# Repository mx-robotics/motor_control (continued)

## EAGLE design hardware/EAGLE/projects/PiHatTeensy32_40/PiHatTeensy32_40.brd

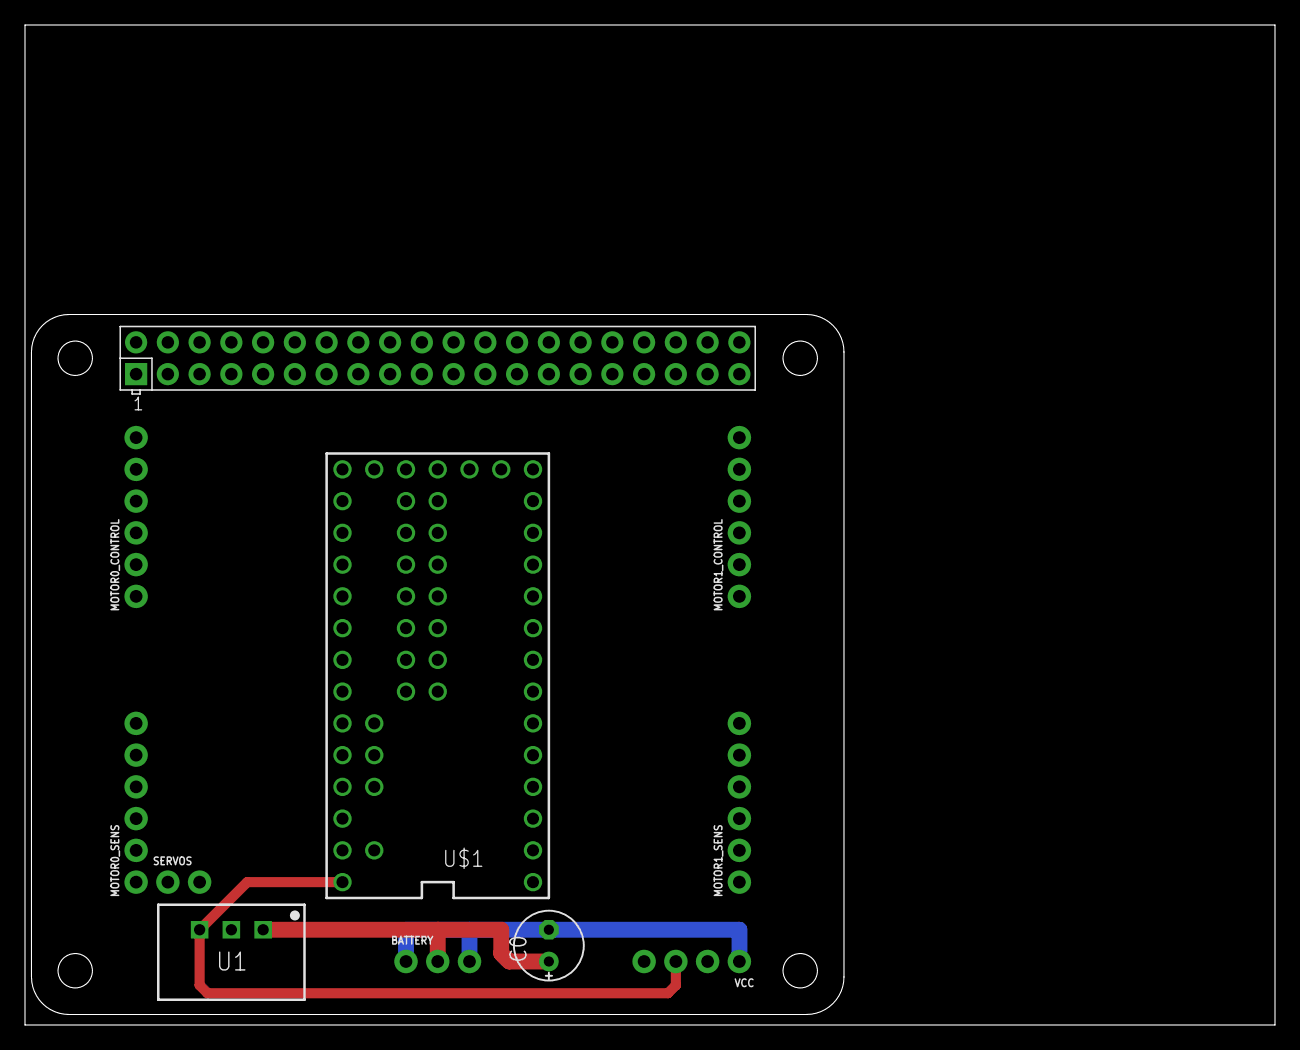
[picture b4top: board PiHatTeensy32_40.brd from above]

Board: 2 copper layers, 100.0 x 80.0 mm, 11 parts (0 on the bottom side), 31 nets.

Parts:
BATTERY: 1X03_NO_SILK
C0: E2,5-6E
MOTOR0_CONTROL, MOTOR0_SENS, MOTOR1_CONTROL, MOTOR1_SENS: 1X06_NO_SILK
SERVOS: 1X02_NO_SILK
U1: TSR_1-2450; TSR-1
U$1: TEENSY_3.1-3.2_ALL_PINS&PADS; TEENSY_3.0-3.2_ALL_PINS_&_PADS
VCC: JP; 1X04_NO_SILK
X1: RASPI_BOARD_B+_H; RASPI_BOARD_B+HAT

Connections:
3.3V: U$1.3.3V, U$1.3.3V1, U$1.3.3V2, VCC.2
5.0V: U1.3, U$1.VIN, VCC.3
GND: BATTERY.1, BATTERY.3, C0.-, U1.2, U$1.GND, U$1.GND1, U$1.GND2, VCC.1, X1.6
HALL_U0: MOTOR0_SENS.1, U$1.0
HALL_U1: MOTOR1_SENS.1, U$1.1
HALL_V0: MOTOR0_SENS.2, U$1.24
HALL_V1: MOTOR1_SENS.2, U$1.2
HALL_W0: MOTOR0_SENS.3, U$1.33
HALL_W1: MOTOR1_SENS.3, U$1.4
I2C0_SCL: U$1.29, X1.5
I2C0_SDA: U$1.30, X1.3
IN_U0: MOTOR0_CONTROL.4, U$1.23/A9
IN_U1: MOTOR1_CONTROL.4, U$1.5
IN_V0: MOTOR0_CONTROL.5, U$1.22/A8
IN_V1: MOTOR1_CONTROL.5, U$1.6
IN_W0: MOTOR0_CONTROL.6, U$1.21/A7
IN_W1: MOTOR1_CONTROL.6, U$1.10
IS_U0: MOTOR0_SENS.4, U$1.20/A6
IS_U1: MOTOR1_SENS.4, U$1.26
IS_V0: MOTOR0_SENS.5, U$1.19/A5
IS_V1: MOTOR1_SENS.5, U$1.27
IS_W0: MOTOR0_SENS.6, U$1.18/A4
IS_W1: MOTOR1_SENS.6, U$1.28
SERVO_0: SERVOS.1, U$1.32
SERVO_1: SERVOS.2, U$1.25
SPI_CS0: U$1.15/A1, X1.24
SPI_CS1: U$1.31, X1.26
SPI_MISO: U$1.12, X1.21
SPI_MOSI: U$1.11, X1.19
SPI_SCLK: U$1.14/A0, X1.23
VI: BATTERY.2, C0.+, U1.1

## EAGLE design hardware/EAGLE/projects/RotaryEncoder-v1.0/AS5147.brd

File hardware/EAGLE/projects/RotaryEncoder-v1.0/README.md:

PCB for AMS (Austrian Micro Devices) Magnetic Position Sensors.

The physical interface fits the following devices:

1) AS5147P (https://ams.com/as5147p)

2) AS5047P (https://ams.com/as5047p)

3) AS5147 (https://ams.com/as5147)

4) AS5047D (https://ams.com/as5047d)

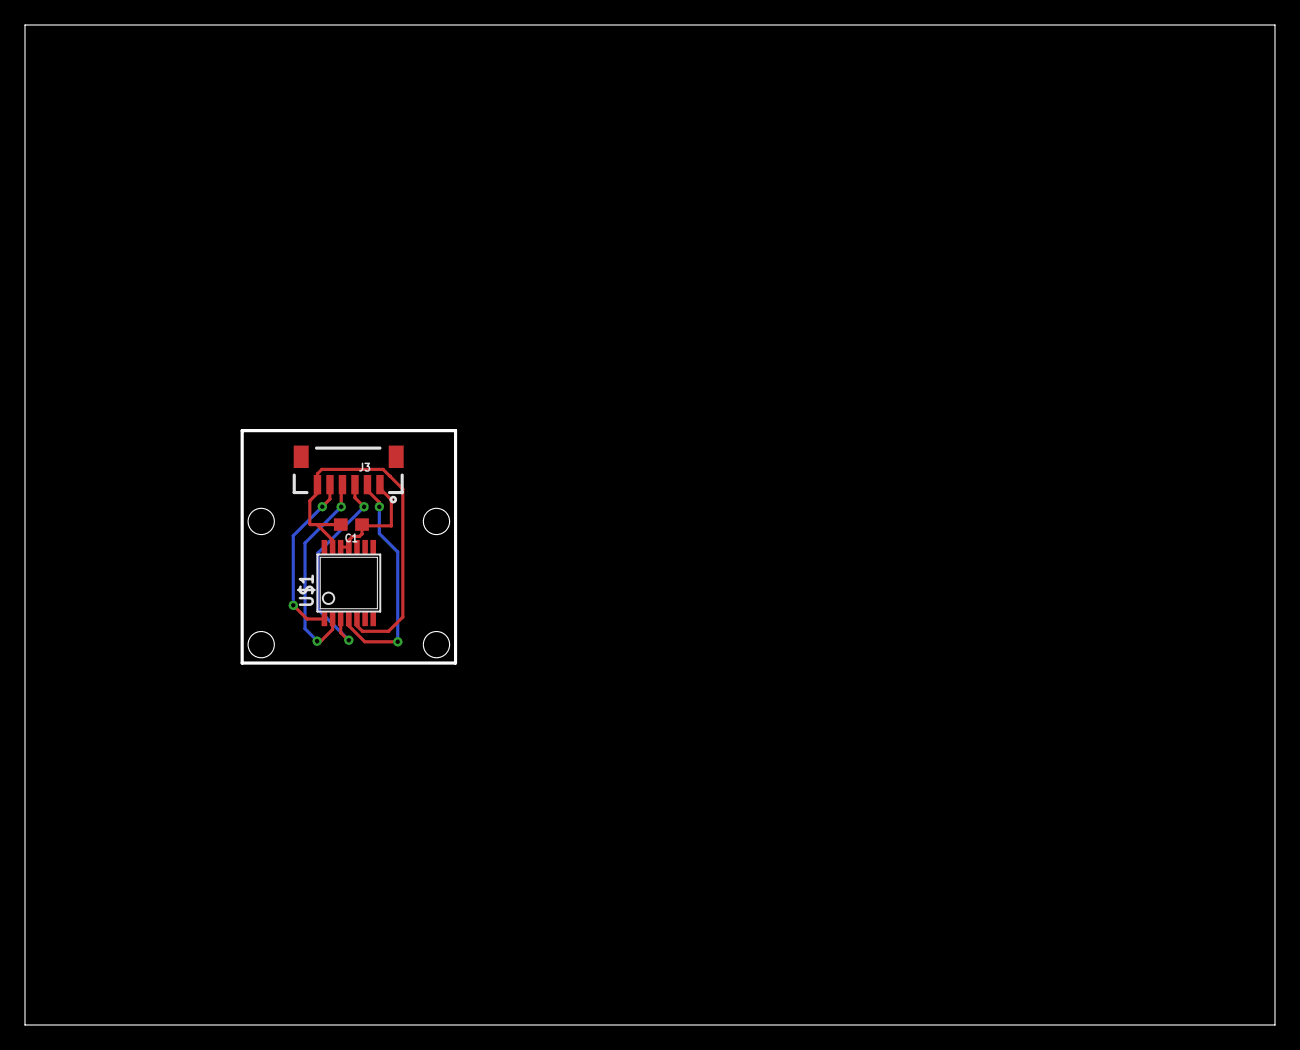
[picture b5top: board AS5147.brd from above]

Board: 2 copper layers, 100.0 x 80.0 mm, 3 parts (0 on the bottom side), 6 nets.

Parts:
C1: 0.1uF; 0603
J3: 1X06-1MM
U$1: TSSOP14

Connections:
3.3V: C1.1, J3.1, U$1.11, U$1.12
CLK: J3.4, U$1.2
CS: J3.5, U$1.1
GND: C1.2, J3.6, U$1.5, U$1.13
MISO: J3.3, U$1.3
MOSI: J3.2, U$1.4

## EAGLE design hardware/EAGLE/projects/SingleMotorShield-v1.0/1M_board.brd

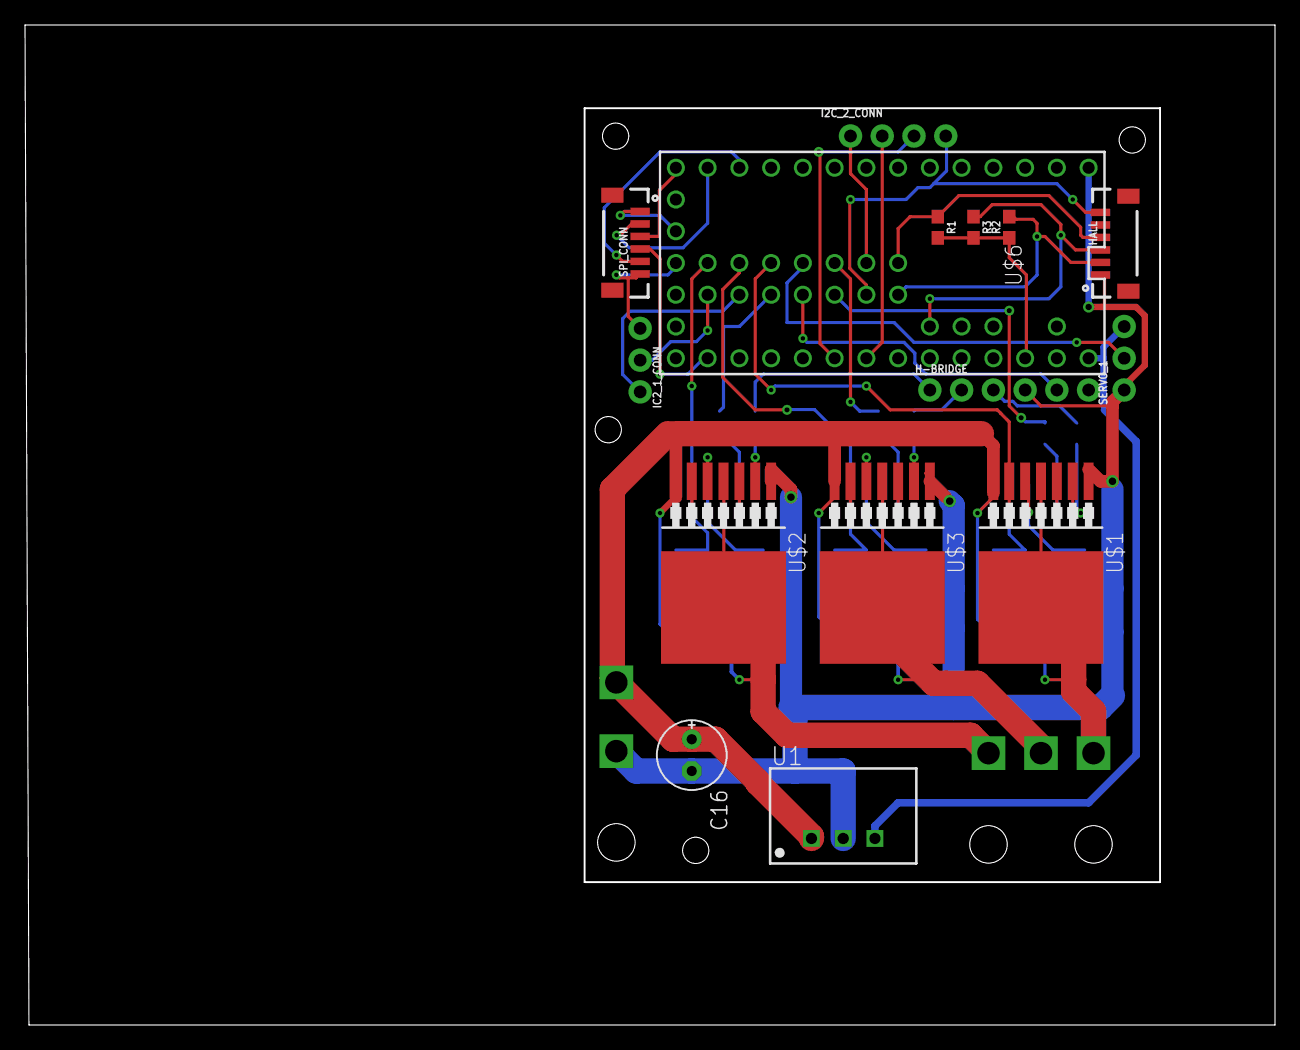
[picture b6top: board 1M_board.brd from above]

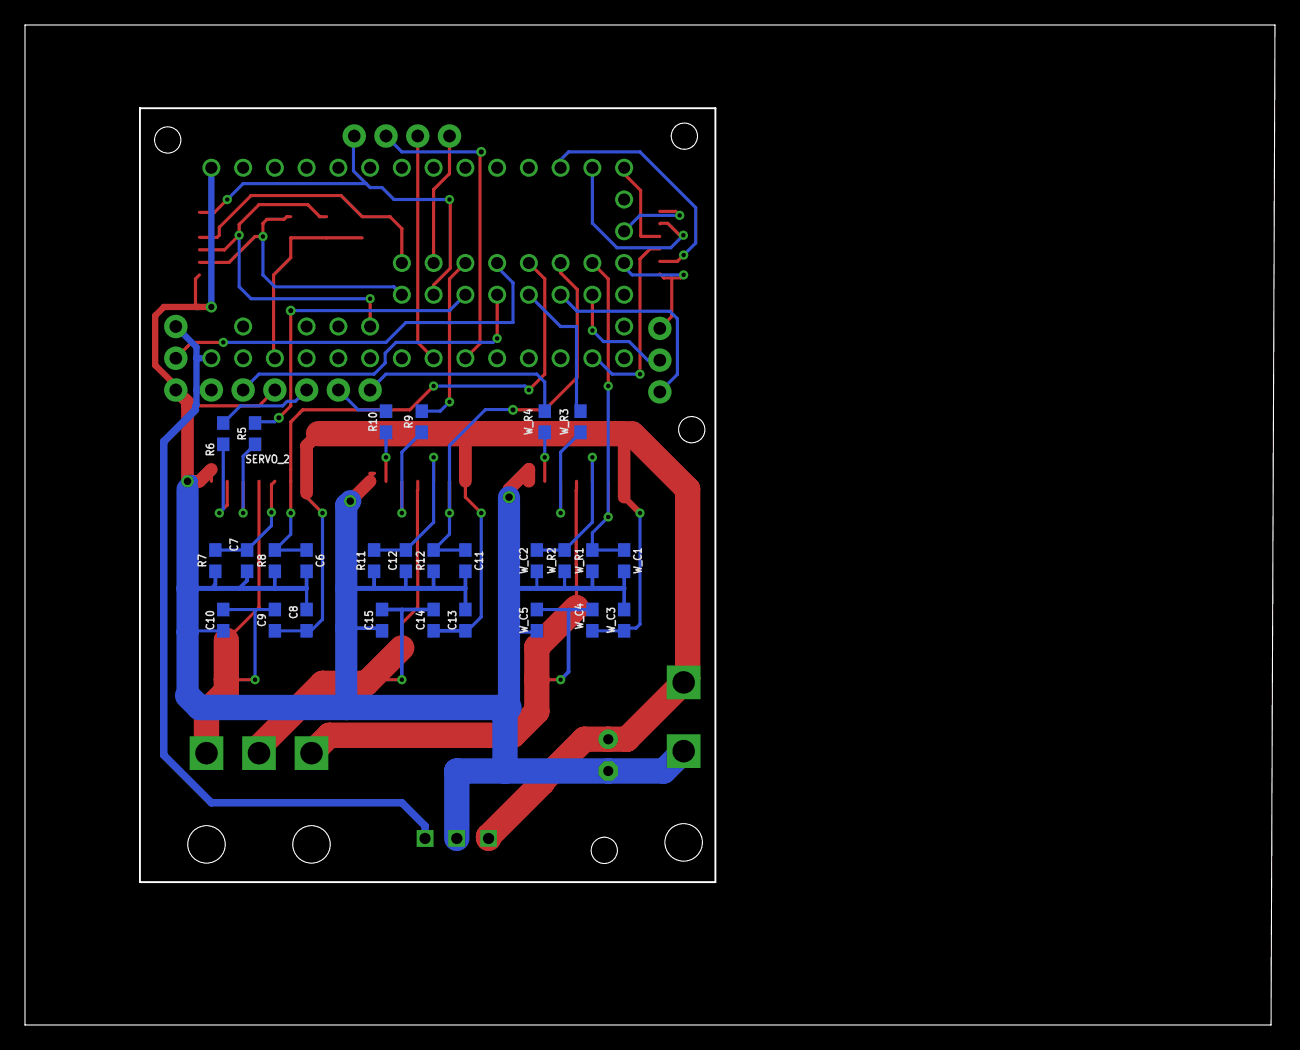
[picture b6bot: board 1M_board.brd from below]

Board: 2 copper layers, 100.0 x 80.0 mm, 45 parts (30 on the bottom side), 38 nets.

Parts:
C6, C8, C11, C13: 0.1uF; 0603
C7, C12: 1nF; 0603
C9, C10, C14, C15: 0.22uF; 0603
C16: 470uF; E2,5-6E
H-BRIDGE: PWM; 1X03_NO_SILK
HALL: 1X06-1MM
I2C_2_CONN: IMU_SENS; 1X04_NO_SILK
IC2_1_CONN: INTEL_BRD; 1X03_NO_SILK
R1, R2, R3, R5, R6, R9, R10: 10k; 0603
R7, R11: 47k; 0603
R8, R12: 4.7k; 0603
SERVO_1, SERVO_2: 1X03_NO_SILK
SPI_CONN: ENCODER; 1X06-1MM
U1: TSR_1-2450; TSR-1
U$1, U$2, U$3: P-TO263-7-1
U$4: 5569-003
U$5: 5569-002
U$6: TEENSY_3.1-3.2_ALL_PINS&PADS; TEENSY_3.0-3.2_ALL_PINS_&_PADS
W_C1, W_C3: 0.1uF; 0603
W_C2: 1nF; 0603
W_C4, W_C5: 0.22uF; 0603
W_R1: 4.7k; 0603
W_R2: 47k; 0603
W_R3, W_R4: 10k; 0603

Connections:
3.3V: HALL.6, I2C_2_CONN.4, R1.2, R2.1, R3.2, SPI_CONN.1, U$6.3.3V, U$6.3.3V1, U$6.3.3V2
CS: SPI_CONN.5, U$6.10
GND: C6.2, C7.1, C8.2, C10.1, C11.2, C12.1, C13.2, C15.1, C16.-, HALL.1, I2C_2_CONN.1, IC2_1_CONN.3, R7.1, R8.1, R11.1, R12.1, SERVO_1.1, SERVO_2.1, SPI_CONN.6, U1.2, U$1.1, U$2.1, U$3.1, U$5.GND, U$6.GND, U$6.GND1, U$6.GND2, W_C1.2, W_C2.1, W_C3.2, W_C5.1, W_R1.1, W_R2.1
HALL_U: HALL.4, R1.1, U$6.A12
HALL_V: HALL.3, R3.1, U$6.A11
HALL_W: HALL.2, R2.2, U$6.A13
INH_U: R5.2, U$6.33
INH_V: R9.2, U$6.24
INH_W: U$6.31, W_R3.2
IN_U: H-BRIDGE.3, R6.2
IN_V: H-BRIDGE.2, R10.2
IN_W: H-BRIDGE.1, W_R4.2
IS_U: C6.1, R8.2, U$1.6, U$6.26
IS_V: C11.1, R12.2, U$3.6, U$6.27
IS_W: U$2.6, U$6.28, W_C1.1, W_R1.2
MISO: SPI_CONN.3, U$6.12
MOSI: SPI_CONN.2, U$6.11
unnamed: U$2.3, W_R3.1
unnamed: C12.2, R11.2, U$3.5
unnamed: U$2.5, W_C2.2, W_R2.2
unnamed: C7.2, R7.2, U$1.5
unnamed: R5.1, U$1.3
unnamed: R6.1, U$1.2
unnamed: R9.1, U$3.3
unnamed: U$2.2, W_R4.1
unnamed: R10.1, U$3.2
SCK: SPI_CONN.4, U$6.14/A0
SCL0: I2C_2_CONN.2, U$6.19/A5
SCL1: IC2_1_CONN.2, U$6.29
SDA0: I2C_2_CONN.3, U$6.18/A4
SDA1: IC2_1_CONN.1, U$6.30
S_PWM_1: SERVO_1.2, U$6.25
S_PWM_2: SERVO_2.2, U$6.32
U: C9.2, C10.2, U$1.4, U$1.8, U$4.U
V: C14.2, C15.2, U$3.4, U$3.8, U$4.V
VCC: SERVO_1.3, SERVO_2.3, U1.3, U$6.VIN
VI: C8.1, C9.1, C13.1, C14.1, C16.+, U1.1, U$1.7, U$2.7, U$3.7, U$5.VCC, W_C3.1, W_C4.1
W: U$2.4, U$2.8, U$4.W, W_C4.2, W_C5.2

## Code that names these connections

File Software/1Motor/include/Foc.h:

//
// Created by firat on 19.01.20.
//
#ifndef DMA_SPI_FOC_H
#define DMA_SPI_FOC_H


#include <SPI.h>
#include <array>
#include <ADC.h>


namespace tuw {

    class FOC {
    public:
        static FOC &getInstance();  // Singleton handler

        void SPITransfer();

        void calculate_offset_parameters();
        void initPins();  // called once in setup
        void doTheMagic(); // called every loop iteration

        void P_controller(float rps_target, float rps_measured);
        void PID_controller(float rps_target, float rps_measured);



        // ########### PID RELATED FUNCTIONS ///////////

        void setSpeedRPM(uint8_t _target_speed);

        // ############# ADC

        void setSpeedFromADC();


        // ######### DEBUG FUNCTIONS ///////

        void printLUToffsetValues();
        void printMaxDutyCylcle();
        void setSpeedSerial();
        void debugPlot();
        std::array<uint16_t , 360> getArray();
        uint16_t getRotorPosition();
        float getMySpeed() const;
        volatile float getTargetSpeed() const;

        void led_foo ();
        void calculateSensorOffsetAngle();
        void getModulationIndexSpeedValues();

        void calculateRPS();








    private:
        FOC();

        // ++++++++++++++initial activation functios
        void initSPI();
        void initInhibitPIN();
        void setPWMpins();
        void initServoPins();
        void activateInhibitPins();

        // ***************** LUT & DUTY CYCLE CALCULATIONS
        void calculateInputPinsDutyCycle(); // on the fly calculation, used once for LUT creation
        inline uint16_t calculate_LUT_offset(); // calculate the modulation index-speed command relation
        std::array<uint16_t , 360> createLUT(); // create the LUT
        void calculate_offset_parameters_short(); // calculates the offset func parameters in a magic way, called 1
        void calculateInputPinsDutyCycleLUT();
        void setInputPinsDutyCycle();

        // ****************** ADC functions
        void initADCconversions();




        // ****************** MATH

        inline int fast_mod(const int input, const int ceil) {
            return input >= ceil ? input % ceil : input; }

        inline float moving_ave(float angle){
            static int i=0;
            static float sum = 0;
            sum -= move_average_list[i];
            move_average_list[i] = angle;
            sum += move_average_list[i];
            i++;
            if (i == 100) {
                i = 0;
            }

            return sum*0.01f;

        }

        // ************* P I N S ******************
        static constexpr uint8_t CS = 10; // has to be static cuz a constexpr must be known at compile time
        static constexpr uint8_t CLK = 14; // if it isn't static, you need to wait runtime until the object is created
        volatile uint16_t rotor_position=0;
        volatile float_t target_rpm=50.f;

        float_t offset_param_m;
        float_t offset_param_c;


        static constexpr uint8_t IS_W= A17;
        static constexpr uint8_t IS_v= A16;
        static constexpr uint8_t IS_U= A15;

        static constexpr uint8_t INH_W= 31;
        static constexpr uint8_t INH_V= 24;
        static constexpr uint8_t INH_U= 33;

        static constexpr uint8_t S_PWM1= 25;
        static constexpr uint8_t S_PWM2= 32;

        static constexpr uint8_t IN_W= 21;
        static constexpr uint8_t IN_V= 22;
        static constexpr uint8_t IN_U= 23;

        // *************** P W M   C O N S T A N T S ****************

        static constexpr uint16_t PWM_FREQ = 20000;
        static constexpr uint16_t MAX_DUTY_CYCLE = (F_BUS/PWM_FREQ)/2;

        volatile uint32_t IN_W_duty_cycle;
        volatile uint32_t IN_U_duty_cycle;
        volatile uint32_t IN_V_duty_cycle;


        static constexpr uint16_t sensor_offset= 180;//85; // 275; //75
        static constexpr uint8_t angle_offset = 95;
        volatile float modulation_index = 1.1547005f;
        volatile int8_t direction = 1; // -1 is CCW


    private:

        const std::array<uint16_t , 360> array = createLUT();
        uint8_t f_to_c_array[160];
        float acc_error = 0;
        std::array<float , 100> move_average_list;


        float target_speed= 60;
        float target_rps= 7.5;
    public:
        volatile float getTargetRps() const;

    private:

        //between o and 100
        volatile uint8_t sensor_overflow = 0;

        volatile uint16_t angle_now=0;

        float my_speed=0.f;

        const SPISettings spiSettings=SPISettings(10000000,MSBFIRST, SPI_MODE1);

        static constexpr uint8_t ADC_PIN = A1;
        ADC *adc = new ADC();
    };

};
#endif //DMA_SPI_FOC_H

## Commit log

2019-05-05 Create RotaryEncoder
2019-05-07 pcb schematics
2019-05-07 pcbs added
2019-05-07 svpwm
2019-05-11 readme
2020-01-18 repo structure changed for future usage
2020-01-18 a working version has been added for 1motor board
2020-01-18 2Motor demo code uploaded
2020-01-18 Hardware revision notes has been added
2020-01-19 update folder structre for easier use with clion and pio
2020-01-21 1Motor_refactor added
2020-01-25 speed calculation updated, added utils and TODO's
2020-01-30 SPI working
2020-01-30 LUT with constexpr
2020-01-31 PWM Duty cycle calculation development
2020-02-01 SVPWM implementation done
2020-02-01 minor changes and TODO list
2020-02-16 spinning with TOF interrupt
2020-02-16 minor changes
2020-02-16 pyton script updated
2020-02-18 - field weakening implemented - spins with the same speed in both directions
2020-02-19 pid boiler plate added, 2. motor seems to be physically unfit
2020-02-26 proper header cpp seperation
2020-02-29 primitive PID working
2020-02-29 function signatures updated
2020-02-29 docs added
2020-03-05 gitignore added
2020-03-05 cleanup
2020-03-05 lib change
2020-03-05 main.c clean up
2020-03-05 spi and adc working again, it might be necessary to use the old SPI lib, so it is added to lib folder for future use just in case
2020-03-07 New SingleBoard Controller revision started
2020-03-08 unneeded eagel files deleted
2020-03-08 Eagle project folder added
2020-03-08 Eagle Projects moved into Eagle Structure
2020-03-08 progress on DualModorShieldOnRaspberryHat
2020-03-08 Dualboard update
2020-03-09 minor updates on DualMotorShield-v3.0
2020-03-11 molex interface changed with simple pins
2020-03-11 adaptive fieldweakening added
2020-03-11 gitignore updated
2020-03-11 removed debug folder
2020-03-11 removed .idea folder
2020-03-11 readme updated
2020-03-11 added TODO for Software
2020-03-11 added IFX007T H-Bridge Application Notes
2020-03-11 added MotorShield libraries for PCBs
2020-03-12 jst header for SPI has been replaces with its vertical counterpart
2020-03-12 Software renamed to software
2020-03-14 DualShield update
2020-03-15 spi update
2020-03-15 Component renamed
2020-03-15 libraries moved
2020-03-15 DualMotorHat added
2020-03-15 Connector for Hat added
2020-03-20 layout update
2020-03-21 progress on MotorHat
2020-03-24 motorhad finished
2020-03-26 Pin renamings, got rid of redundant SPI struct, replaced with just CS pin
2020-03-28 vcc jumper update
2020-03-28 files renamed
2020-03-28 teensy32 board added
2020-03-28 schematic connection done, pins 16-17 should be wired to UART
2020-03-30 PiHat update
2020-03-30 PinUsage update
2020-03-31 latest changes
2020-04-01 Befour autorouting
2020-04-01 PiHatMotorController checked
2020-04-01 wired HALL_V1 to Pin 7
2020-04-01 changed the via position
2020-04-02 cancelled UART, made some cosmetic changes, ready for production
2020-04-02 uart tx tx added back again, more coesmetic changes
2020-04-02 Label added to PiHatTeensy32
2020-04-02 Label added to PiMotorHat
2020-04-02 Version 2020-04 done
2020-04-09 overclocked to 120 MHZ and added -03 optimisations (02 default)
2020-04-11 old board, fixed the scaledRotaryEncoder bug, working fine
2020-04-17 working horrible with the new motor and new board, much to do
2020-04-17 this software version works with both motors, and is an excellent basis for any implementation, the U V and W are configured in such a way that they exactly match hw on the old 1M board
2020-04-17 arranged for the old motor
2020-04-17 old motors somehwat working
2020-04-17 old motors working (also not in a nice way) with the new board, tried just 0 side
2020-04-17 works with both motors but with a terrybad performance
2020-04-17 gitignore update
2020-04-19 function signature and phase ordering changed to reflect the other parts
2020-04-19 function signature change
2020-05-13 with sensor offset 200 new motors work but the torque is very low and there is no smooth motion, rather full of vibrations
2020-05-13 same as 2mBoard branch
2020-05-13 updated pwm pins
2020-05-28 chngs
2020-05-30 defines for the new board added
2020-05-30 pins for the motor0 and motor1 added
2020-05-30 motor registiration for the new board, put in #define
2020-05-30 initHardware function updated to take the SPI CLK pin as input
2020-05-30 initPWMPins() function updated for the new board
2020-05-30 added the PWM pin duty cycle update for the new board pins -> modified updatePWMPinsDutyCycle() fuction
2020-05-31 cosmetic changes
2020-05-31 function documentations added
2020-07-10 new board with new motors working with acceptable performance
2020-07-26 repo re-structure for easier pio-clion integration
2020-07-26 removed the second software folder, updated structure
2020-08-08 new speed measurement working more accurately with lower speeds
2020-08-27 calibration for both motors has been done, both motors are spinning in matching speeds
2020-08-27 servo controller added
2020-08-27 function to get servo, direction and velocity from serial added
2020-08-27 repo clean up, older code for 1M and 2M boards removed
2020-08-27 more repo restructure, moved every other helper software under /utilities
2020-08-27 todos and docs added, needs a clean up
2020-08-27 software utils added
2020-08-28 ros node added for joystick control
2020-08-28 readme.md update
2020-08-28 Teensy low level drivers carried to their respective class
2020-08-29 diagnostic and serial related functions moved under utils.h from FOC
2020-08-29 FOC renamed to Controller, funtions in SVPWM moved from header to cpp file
2020-08-29 LUT generator moved to its own header file
2020-08-29 derivative filter implemented
2020-08-30 pid counter changed
2020-08-30 hardcoded values replaced with compile flags
2020-09-25 last
